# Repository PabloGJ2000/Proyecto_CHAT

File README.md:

# Proyecto_CHAT
By Pablo García Jaén
MoaisEnergy.com
Open source

Funciones actualmente operativas:
-Suma
-Resta
-Multiplicación
-División
-Potencias
-Raices cuadradas
-Raices de cualquier número
-Logaritmo en base diez
-Logaritmo neperiano
-Seno
-Coseno
-Tangente
-Paréntesis

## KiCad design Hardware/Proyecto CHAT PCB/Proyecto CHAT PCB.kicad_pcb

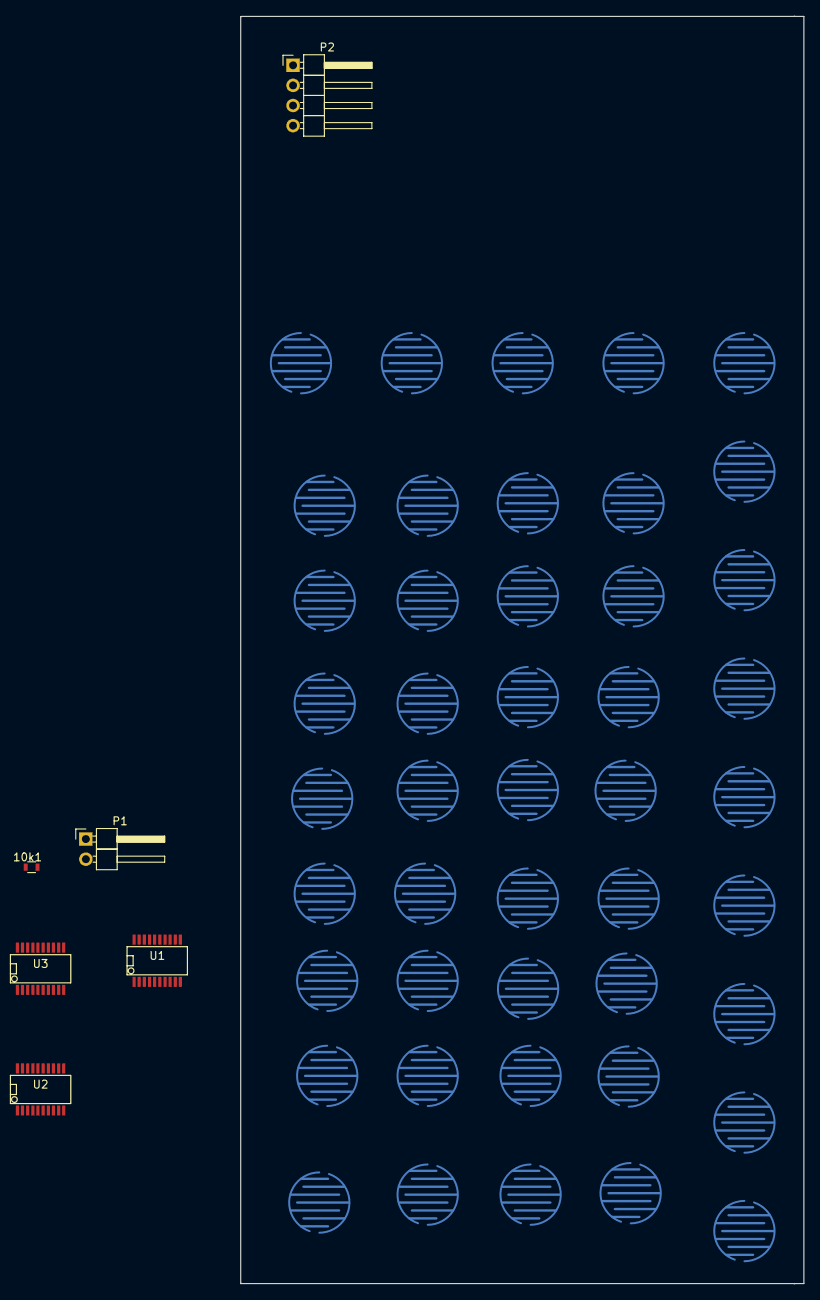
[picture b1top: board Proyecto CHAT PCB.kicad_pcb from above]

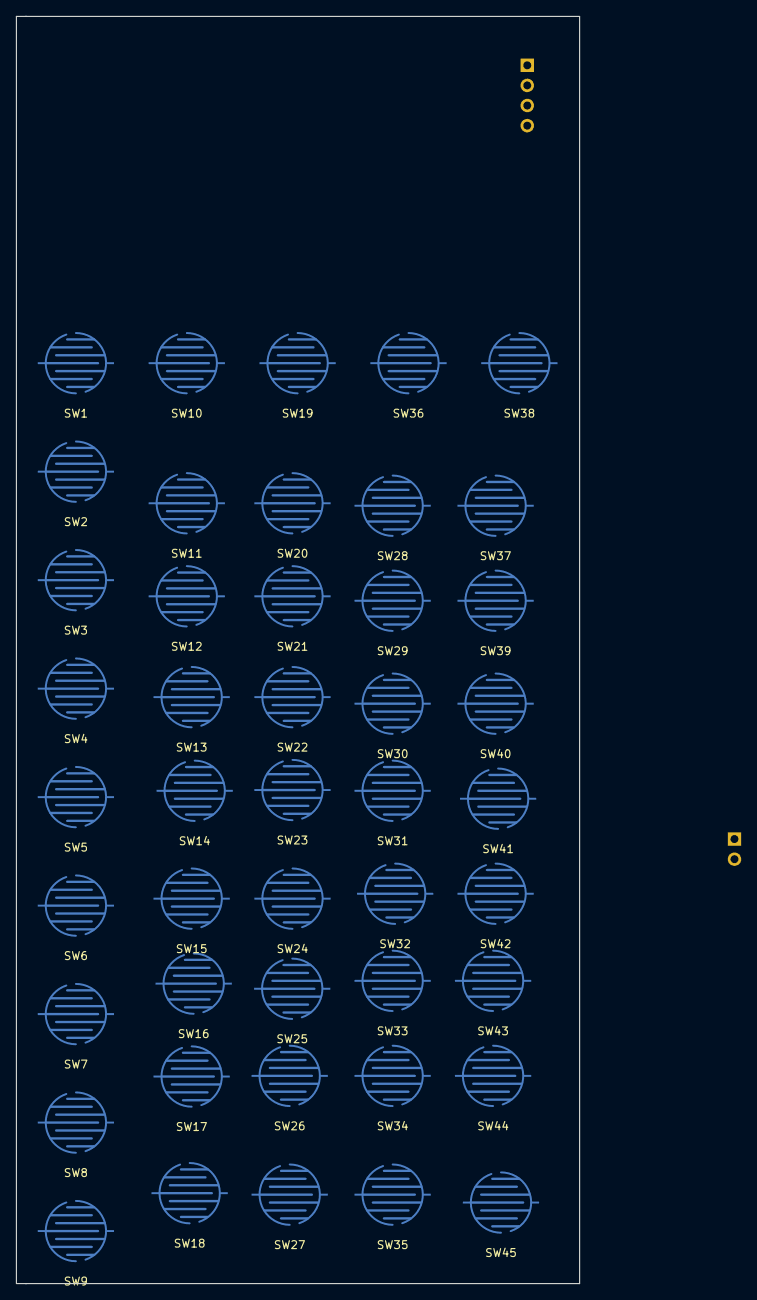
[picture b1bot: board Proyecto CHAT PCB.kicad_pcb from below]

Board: 2 copper layers, 71.1 x 160.0 mm, 51 parts (45 on the bottom side), 20 nets, no tracks yet.

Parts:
10k1: R; R_0603
P1: CONN_01X02; Pin_Header_Angled_1x02_Pitch2.54mm
P2: CONN_01X04; Pin_Header_Angled_1x04_Pitch2.54mm
SW1: B01; button rubber pad
SW2: B06; button rubber pad
SW3: B11; button rubber pad
SW4: B16; button rubber pad
SW5: B21; button rubber pad
SW6: B26; button rubber pad
SW7: B31; button rubber pad
SW8: B36; button rubber pad
SW9: B41; button rubber pad
SW10: B02; button rubber pad
SW11: B07; button rubber pad
SW12: B12; button rubber pad
SW13: B17; button rubber pad
SW14: B22; button rubber pad
SW15: B27; button rubber pad
SW16: B32; button rubber pad
SW17: B37; button rubber pad
SW18: B42; button rubber pad
SW19: B03; button rubber pad
SW20: B08; button rubber pad
SW21: B13; button rubber pad
SW22: B18; button rubber pad
SW23: B23; button rubber pad
SW24: B28; button rubber pad
SW25: B33; button rubber pad
SW26: B38; button rubber pad
SW27: B43; button rubber pad
SW28: B09; button rubber pad
SW29: B14; button rubber pad
SW30: B19; button rubber pad
SW31: B24; button rubber pad
SW32: B29; button rubber pad
SW33: B34; button rubber pad
SW34: B39; button rubber pad
SW35: B44; button rubber pad
SW36: B04; button rubber pad
SW37: B10; button rubber pad
SW38: B05; button rubber pad
SW39: B15; button rubber pad
SW40: B20; button rubber pad
SW41: B25; button rubber pad
SW42: B30; button rubber pad
SW43: B35; button rubber pad
SW44: B40; button rubber pad
SW45: B45; button rubber pad
U1, U2, U3: MCP23008_SSOP; SSOP-20

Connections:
+3V3: U1.20, U2.20, U3.20
+5V: P1.2, P2.2, U1.3, U1.4, U1.5, U2.3, U3.3, U3.4
/A0: 10k1.1, P1.1
/COL1: SW1.1, SW2.1, SW3.1, SW4.1, SW5.1, SW6.1, SW7.1, SW8.1, SW9.1, U1.12, U2.12, U3.12
/COL2: SW10.1, SW11.1, SW12.1, SW13.1, SW14.1, SW15.1, SW16.1, SW17.1, SW18.1, U1.13, U2.13, U3.13
/COL3: SW19.1, SW20.1, SW21.1, SW22.1, SW23.1, SW24.1, SW25.1, SW26.1, SW27.1, U1.14, U2.14, U3.14
/COL4: SW28.1, SW29.1, SW30.1, SW31.1, SW32.1, SW33.1, SW34.1, SW35.1, SW36.1, U1.15, U2.15, U3.15
/COL5: SW37.1, SW38.1, SW39.1, SW40.1, SW41.1, SW42.1, SW43.1, SW44.1, SW45.1, U1.16, U2.16, U3.16
/FIL1: SW1.2, SW10.2, SW19.2, SW36.2, SW38.2, U1.17
/FIL2: SW2.2, SW11.2, SW20.2, SW28.2, SW37.2, U1.18
/FIL3: SW3.2, SW12.2, SW21.2, SW29.2, SW39.2, U1.19
/FIL4: SW4.2, SW13.2, SW22.2, SW30.2, SW40.2, U2.17
/FIL5: SW5.2, SW14.2, SW23.2, SW31.2, SW41.2, U2.18
/FIL6: SW6.2, SW15.2, SW24.2, SW32.2, SW42.2, U2.19
/FIL7: SW7.2, SW16.2, SW25.2, SW33.2, SW43.2, U3.17
/FIL8: SW8.2, SW17.2, SW26.2, SW34.2, SW44.2, U3.18
/FIL9: SW9.2, SW18.2, SW27.2, SW35.2, SW45.2, U3.19
/SCL: P2.4, U1.1, U2.1, U3.1
/SDA: P2.3, U1.2, U2.2, U3.2
GND: 10k1.2, P2.1, U1.9, U2.4, U2.5, U2.9, U3.5, U3.9

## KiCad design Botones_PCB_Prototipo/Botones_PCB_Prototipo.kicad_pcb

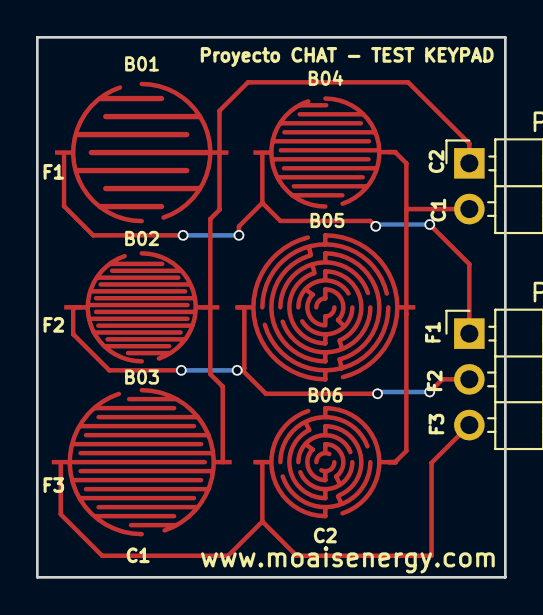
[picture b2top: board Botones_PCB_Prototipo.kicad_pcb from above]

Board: 2 copper layers, 26.0 x 30.0 mm, 8 parts (0 on the bottom side), 5 nets.

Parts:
B01: SW_DIP_x01; button rubber pad
B02: SW_DIP_x01; Button_V2
B03: SW_DIP_x01; Button_V3
B04: SW_DIP_x01; Button_V4
B05: SW_DIP_x01; Button_V5
B06: SW_DIP_x01; Button_V6.1
P1: CONN_01X02; Pin_Header_Angled_1x02_Pitch2.54mm
P2: CONN_01X03; Pin_Header_Angled_1x03_Pitch2.54mm

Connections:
unnamed: B01.1, B02.1, B03.1, P1.1
unnamed: B04.1, B05.1, B06.1, P1.2
unnamed: B01.2, B04.2, P2.1
unnamed: B02.2, B05.2, P2.2
unnamed: B03.2, B06.2, P2.3

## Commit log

2017-04-11 Version con Parentesis funcionales
2017-04-11 Es posible restar
2017-04-11 Multiplicación, división y potencia añadidos
2017-04-13 numeros decimales añadidos
2017-05-05 raices cuadradas y operaciones con números decimales añadidos
2017-05-05 ya se puede hacer cualquier raiz
2017-05-06 logaritmo de base diez, logaritmo neperiano, seno, coseno y tangente añadidos
2017-05-11 Bugs en numeros decimales negativos arreglados
2017-06-24 Añadido: navegación por la pantalla LCD + representación de caracter (raiz cuadrada). Resuelto: problemas al sustituir paréntesis
2017-06-25 Añadido: disponible el número e y el número pi. También se han añadido caracteres para mostrar por la pantalla LCD (raiz de cualquier número, número pi y número e)
2017-06-25 Añadido: arcoseno, arcocoseno, arcotangente + sus respectivos símbolos en la pantalla LCD. Arreglado: bug al moverse hacia la derecha
2017-07-13 Solucionado problemas. La mayoría solucionados gracias al cambio del Arduino Nano por una placa Feather M0 de Adafruit.
2017-07-14 Solucionado problema que provocaba un pequeño delay al escribir en la pantalla. También solucionado problema de escribir PI*x e*x (siendo x cualquier número). Añadido ANS.
2017-07-20 añadido deslizamiento del string al escribir +16 caracteres
2017-07-20 subido
2017-09-27 gcopia personal
